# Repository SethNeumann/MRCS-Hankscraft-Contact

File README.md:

MRCS-Hankscraft-Contact

## License: Creative Commons Attribution-NonCommercial-ShareAlike

Microswitch Contact and contact mutiplier for Hankscraft Switch Motor, requested by Allison Dendy

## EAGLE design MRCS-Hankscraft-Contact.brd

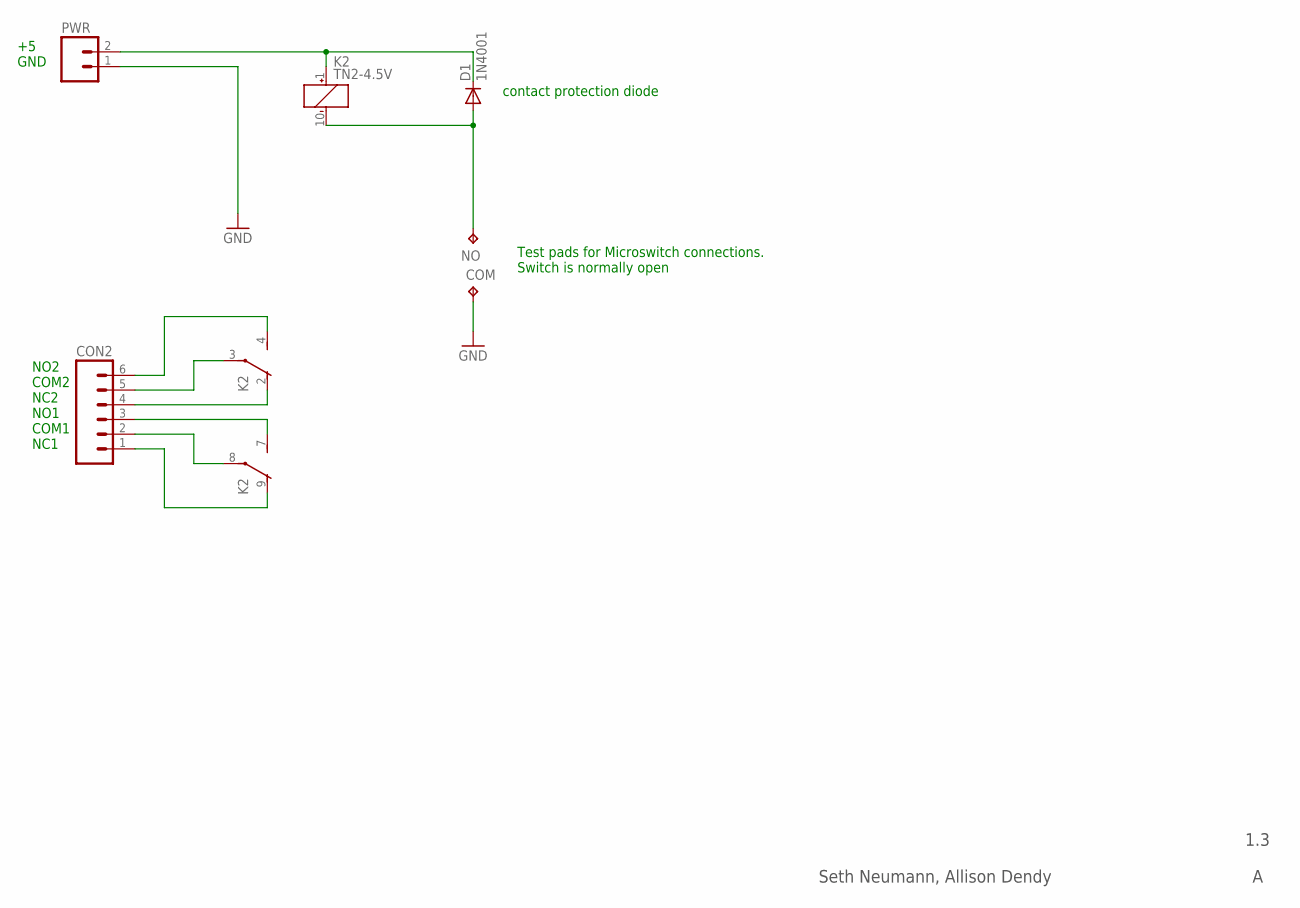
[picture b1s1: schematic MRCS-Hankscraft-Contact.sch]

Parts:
COM: TPPAD1-13; P1-13
CON2: CONNECTOR-M06LOCK; 1X06_LOCK
D1: 1N4001; DIODE-1N4001
K2: TN2-4.5V; TN2
NO: TPPAD1-13; P1-13
PWR: CONNECTOR-M021X02-LOCK; 1X02_LOCK

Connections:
GND: COM.TP, PWR.1 (A)
unnamed: CON2.2, K2.8
unnamed: CON2.3, K2.7 (S)
unnamed: CON2.1, K2.9 (O)
unnamed: CON2.4, K2.2 (O)
unnamed: CON2.5, K2.3
unnamed: CON2.6, K2.4 (S)
unnamed: D1.C, K2.1 (+), PWR.2 (B)
unnamed: D1.A, K2.10 (-), NO.TP

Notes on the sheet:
1.3
Seth Neumann, Allison Dendy
+5 GND
contact protection diode
NO2 COM2 NC2 NO1 COM1 NC1
Test pads for Microswitch connections. Switch is normally open

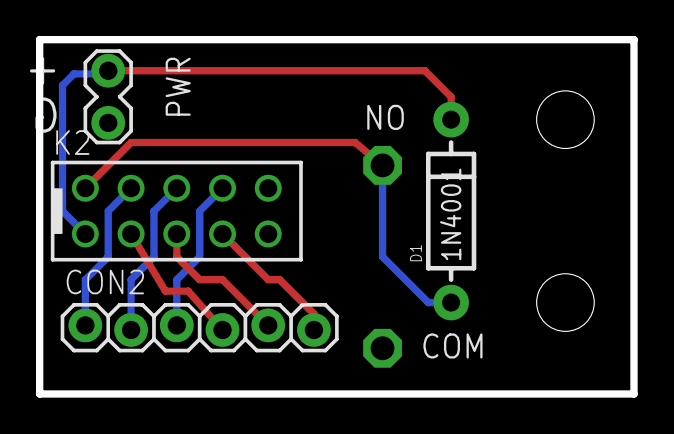
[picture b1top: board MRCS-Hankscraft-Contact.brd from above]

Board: 2 copper layers, 33.0 x 19.7 mm, 7 parts (0 on the bottom side), 9 nets.

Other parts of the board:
U$1: MRCSLOGOTOP

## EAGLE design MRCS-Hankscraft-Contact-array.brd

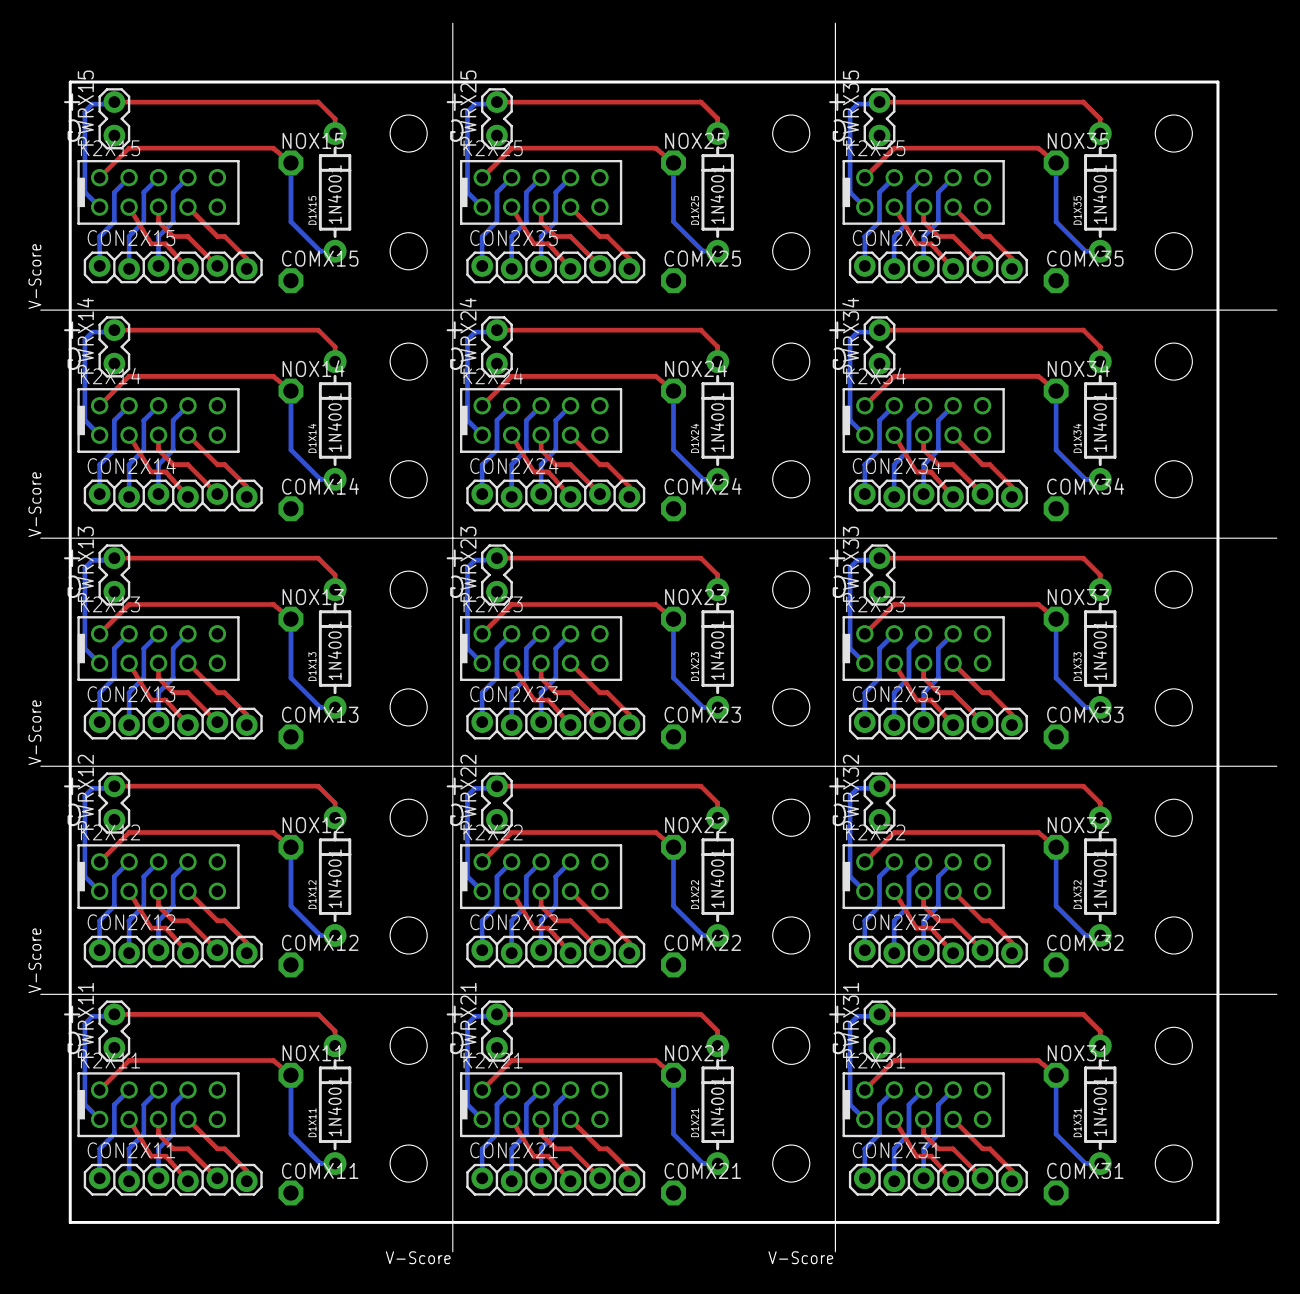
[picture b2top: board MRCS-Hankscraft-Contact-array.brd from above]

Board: 2 copper layers, 107.9 x 107.4 mm, 105 parts (0 on the bottom side), 135 nets.

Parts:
COMX11, COMX12, COMX13, COMX14, COMX15, COMX21, COMX22, COMX23, COMX24, COMX25, COMX31, COMX32, COMX33, COMX34, COMX35: TPPAD1-13; P1-13
CON2X11, CON2X12, CON2X13, CON2X14, CON2X15, CON2X21, CON2X22, CON2X23, CON2X24, CON2X25, CON2X31, CON2X32, CON2X33, CON2X34, CON2X35: 1X06_LOCK
D1X11, D1X12, D1X13, D1X14, D1X15, D1X21, D1X22, D1X23, D1X24, D1X25, D1X31, D1X32, D1X33, D1X34, D1X35: 1N4001; DIODE-1N4001
K2X11, K2X12, K2X13, K2X14, K2X15, K2X21, K2X22, K2X23, K2X24, K2X25, K2X31, K2X32, K2X33, K2X34, K2X35: TN2-4.5V; TN2
NOX11, NOX12, NOX13, NOX14, NOX15, NOX21, NOX22, NOX23, NOX24, NOX25, NOX31, NOX32, NOX33, NOX34, NOX35: TPPAD1-13; P1-13
PWRX11, PWRX12, PWRX13, PWRX14, PWRX15, PWRX21, PWRX22, PWRX23, PWRX24, PWRX25, PWRX31, PWRX32, PWRX33, PWRX34, PWRX35: 1X02_LOCK
U$1X11, U$1X12, U$1X13, U$1X14, U$1X15, U$1X21, U$1X22, U$1X23, U$1X24, U$1X25, U$1X31, U$1X32, U$1X33, U$1X34, U$1X35: MRCSLOGOTOP

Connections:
GNDX11: COMX11.TP, PWRX11.1
GNDX12: COMX12.TP, PWRX12.1
GNDX13: COMX13.TP, PWRX13.1
GNDX14: COMX14.TP, PWRX14.1
GNDX15: COMX15.TP, PWRX15.1
GNDX21: COMX21.TP, PWRX21.1
GNDX22: COMX22.TP, PWRX22.1
GNDX23: COMX23.TP, PWRX23.1
GNDX24: COMX24.TP, PWRX24.1
GNDX25: COMX25.TP, PWRX25.1
GNDX31: COMX31.TP, PWRX31.1
GNDX32: COMX32.TP, PWRX32.1
GNDX33: COMX33.TP, PWRX33.1
GNDX34: COMX34.TP, PWRX34.1
GNDX35: COMX35.TP, PWRX35.1
unnamed: CON2X11.2, K2X11.8
unnamed: CON2X12.2, K2X12.8
unnamed: CON2X13.2, K2X13.8
unnamed: CON2X14.2, K2X14.8
unnamed: CON2X15.2, K2X15.8
unnamed: CON2X21.2, K2X21.8
unnamed: CON2X22.2, K2X22.8
unnamed: CON2X23.2, K2X23.8
unnamed: CON2X24.2, K2X24.8
unnamed: CON2X25.2, K2X25.8
unnamed: CON2X31.2, K2X31.8
unnamed: CON2X32.2, K2X32.8
unnamed: CON2X33.2, K2X33.8
unnamed: CON2X34.2, K2X34.8
unnamed: CON2X35.2, K2X35.8
unnamed: CON2X11.3, K2X11.7
unnamed: CON2X12.3, K2X12.7
unnamed: CON2X13.3, K2X13.7
unnamed: CON2X14.3, K2X14.7
unnamed: CON2X15.3, K2X15.7
unnamed: CON2X21.3, K2X21.7
unnamed: CON2X22.3, K2X22.7
unnamed: CON2X23.3, K2X23.7
unnamed: CON2X24.3, K2X24.7
unnamed: CON2X25.3, K2X25.7
unnamed: CON2X31.3, K2X31.7
unnamed: CON2X32.3, K2X32.7
unnamed: CON2X33.3, K2X33.7
unnamed: CON2X34.3, K2X34.7
unnamed: CON2X35.3, K2X35.7
unnamed: CON2X11.1, K2X11.9
unnamed: CON2X12.1, K2X12.9
unnamed: CON2X13.1, K2X13.9
unnamed: CON2X14.1, K2X14.9
unnamed: CON2X15.1, K2X15.9
unnamed: CON2X21.1, K2X21.9
unnamed: CON2X22.1, K2X22.9
unnamed: CON2X23.1, K2X23.9
unnamed: CON2X24.1, K2X24.9
unnamed: CON2X25.1, K2X25.9
unnamed: CON2X31.1, K2X31.9
unnamed: CON2X32.1, K2X32.9
unnamed: CON2X33.1, K2X33.9
unnamed: CON2X34.1, K2X34.9
unnamed: CON2X35.1, K2X35.9
unnamed: CON2X11.4, K2X11.2
unnamed: CON2X12.4, K2X12.2
unnamed: CON2X13.4, K2X13.2
unnamed: CON2X14.4, K2X14.2
unnamed: CON2X15.4, K2X15.2
unnamed: CON2X21.4, K2X21.2
unnamed: CON2X22.4, K2X22.2
unnamed: CON2X23.4, K2X23.2
unnamed: CON2X24.4, K2X24.2
unnamed: CON2X25.4, K2X25.2
unnamed: CON2X31.4, K2X31.2
unnamed: CON2X32.4, K2X32.2
unnamed: CON2X33.4, K2X33.2
unnamed: CON2X34.4, K2X34.2
unnamed: CON2X35.4, K2X35.2
unnamed: CON2X11.5, K2X11.3
unnamed: CON2X12.5, K2X12.3
unnamed: CON2X13.5, K2X13.3
unnamed: CON2X14.5, K2X14.3
unnamed: CON2X15.5, K2X15.3
unnamed: CON2X21.5, K2X21.3
unnamed: CON2X22.5, K2X22.3
unnamed: CON2X23.5, K2X23.3
unnamed: CON2X24.5, K2X24.3
unnamed: CON2X25.5, K2X25.3
unnamed: CON2X31.5, K2X31.3
unnamed: CON2X32.5, K2X32.3
unnamed: CON2X33.5, K2X33.3
unnamed: CON2X34.5, K2X34.3
unnamed: CON2X35.5, K2X35.3
unnamed: CON2X11.6, K2X11.4
unnamed: CON2X12.6, K2X12.4
unnamed: CON2X13.6, K2X13.4
unnamed: CON2X14.6, K2X14.4
unnamed: CON2X15.6, K2X15.4
unnamed: CON2X21.6, K2X21.4
unnamed: CON2X22.6, K2X22.4
unnamed: CON2X23.6, K2X23.4
unnamed: CON2X24.6, K2X24.4
unnamed: CON2X25.6, K2X25.4
unnamed: CON2X31.6, K2X31.4
unnamed: CON2X32.6, K2X32.4
unnamed: CON2X33.6, K2X33.4
unnamed: CON2X34.6, K2X34.4
unnamed: CON2X35.6, K2X35.4
unnamed: D1X11.C, K2X11.1, PWRX11.2
unnamed: D1X12.C, K2X12.1, PWRX12.2
unnamed: D1X13.C, K2X13.1, PWRX13.2
unnamed: D1X14.C, K2X14.1, PWRX14.2
unnamed: D1X15.C, K2X15.1, PWRX15.2
unnamed: D1X21.C, K2X21.1, PWRX21.2
unnamed: D1X22.C, K2X22.1, PWRX22.2
unnamed: D1X23.C, K2X23.1, PWRX23.2
unnamed: D1X24.C, K2X24.1, PWRX24.2
unnamed: D1X25.C, K2X25.1, PWRX25.2
unnamed: D1X31.C, K2X31.1, PWRX31.2
unnamed: D1X32.C, K2X32.1, PWRX32.2
unnamed: D1X33.C, K2X33.1, PWRX33.2
unnamed: D1X34.C, K2X34.1, PWRX34.2
unnamed: D1X35.C, K2X35.1, PWRX35.2
unnamed: D1X11.A, K2X11.10, NOX11.TP
unnamed: D1X12.A, K2X12.10, NOX12.TP
unnamed: D1X13.A, K2X13.10, NOX13.TP
unnamed: D1X14.A, K2X14.10, NOX14.TP
unnamed: D1X15.A, K2X15.10, NOX15.TP
unnamed: D1X21.A, K2X21.10, NOX21.TP
unnamed: D1X22.A, K2X22.10, NOX22.TP
unnamed: D1X23.A, K2X23.10, NOX23.TP
unnamed: D1X24.A, K2X24.10, NOX24.TP
unnamed: D1X25.A, K2X25.10, NOX25.TP
unnamed: D1X31.A, K2X31.10, NOX31.TP
unnamed: D1X32.A, K2X32.10, NOX32.TP
unnamed: D1X33.A, K2X33.10, NOX33.TP
unnamed: D1X34.A, K2X34.10, NOX34.TP
unnamed: D1X35.A, K2X35.10, NOX35.TP

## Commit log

2023-01-03 inital commit
    Initial commit. mounting holes for microswitch, pads for DPDT relay, 0.100 pads for screw term or other 0.100 connector
2023-01-03 initial commit
    Switch and contact multiplier for Hankscraft motor
2023-01-03 inital setup
2023-01-04 first version
    reviewed by Allison, we'll send out for a small batch for testing
2023-01-06 First release sent out to fab
    I'll send these to Allison for testing
2023-01-30 Version 2
    changed size to give the uSwitch pads more room, removed footprint for toggle switch, just using test point pads for connections.
2023-01-30 V1.1 changes
2023-07-05 adding back to Github - disappeared
